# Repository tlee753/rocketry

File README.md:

# rocketry
Rocket Launch Code for Raspberry Pi Zero W

### Setup
1) install pip3
- `sudo apt install python3-pip`

2) install radio libraries
```bash
pip3 install board
pip3 install RPI.GPIO
pip3 install adafruit-blinka
pip3 install adafruit-circuitpython-rfm9x
```

3) enable SPI/I2C
- `sudo raspi-config`
  - `interface options`
- test with `python3 interfaceTest.py`

4) Connect Hardware
- `python3 pingTest.py`

5) Run python files at launch

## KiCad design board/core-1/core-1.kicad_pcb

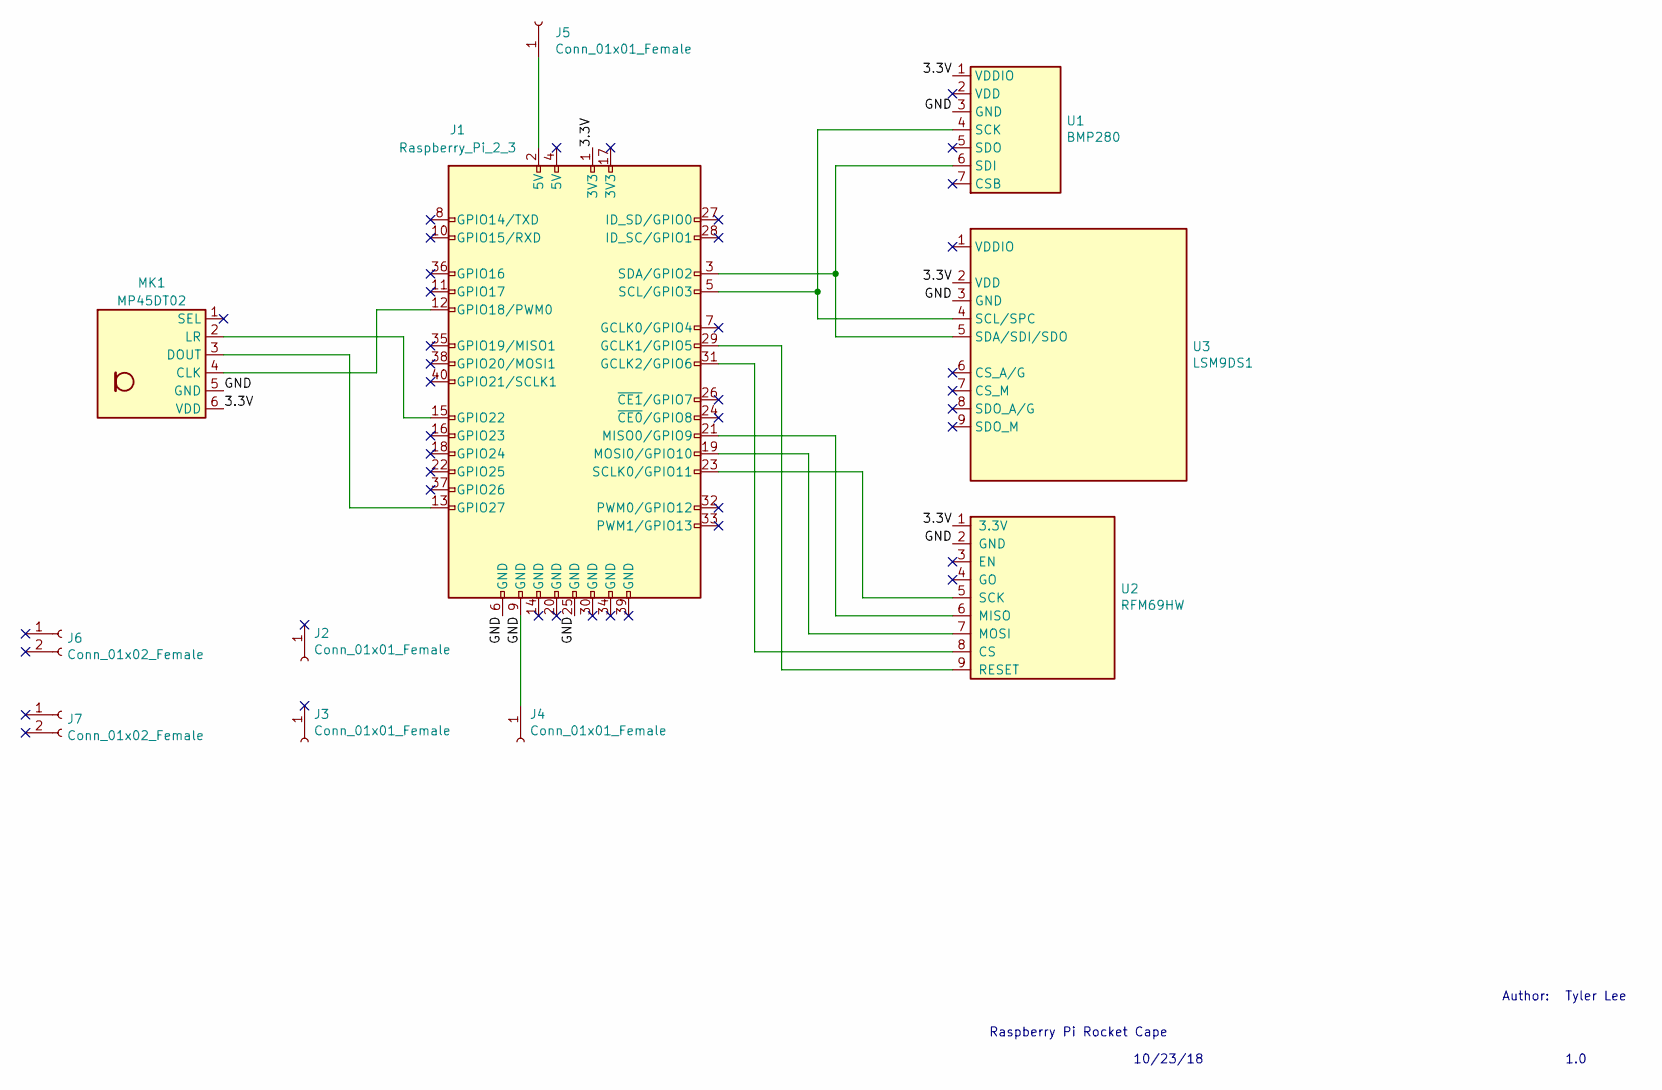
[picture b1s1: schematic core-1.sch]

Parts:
J1: Raspberry_Pi_2_3; IDC-Header_2x20_P2.54mm_Vertical
J2, J3, J4, J5: Conn_01x01_Female; PinHeader_1x01_P2.54mm_Horizontal
J6, J7: Conn_01x02_Female; PinHeader_1x02_P2.54mm_Horizontal
MK1: MP45DT02; PinHeader_1x06_P2.54mm_Vertical
U1: BMP280; PinHeader_1x07_P2.54mm_Vertical
U2: RFM69HW; PinSocket_1x09_P2.54mm_Vertical
U3: LSM9DS1; PinHeader_1x09_P2.54mm_Vertical

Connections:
/3.3V: J1.1 (3V3), MK1.6 (VDD), U1.1 (VDDIO), U2.1 (3.3V), U3.2 (VDD)
/GND: J1.6 (GND), J1.9 (GND), J1.25 (GND), J4.1, MK1.5 (GND), U1.3 (GND), U2.2 (GND), U3.3 (GND)
unnamed: J1.2 (5V), J5.1
unnamed: J1.3 (SDA/GPIO2), U1.6 (SDI), U3.5 (SDA/SDI/SDO)
unnamed: J1.5 (SCL/GPIO3), U1.4 (SCK), U3.4 (SCL/SPC)
unnamed: J1.12 (GPIO18/PWM0), MK1.4 (CLK)
unnamed: J1.13 (GPIO27), MK1.3 (DOUT)
unnamed: J1.15 (GPIO22), MK1.2 (LR)
unnamed: J1.19 (MOSI0/GPIO10), U2.7 (MOSI)
unnamed: J1.21 (MISO0/GPIO9), U2.6 (MISO)
unnamed: J1.23 (SCLK0/GPIO11), U2.5 (SCK)
unnamed: J1.29 (GCLK1/GPIO5), U2.9 (RESET)
unnamed: J1.31 (GCLK2/GPIO6), U2.8 (CS)

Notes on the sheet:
Raspberry Pi Rocket Cape
10/23/18
1.0
Tyler Lee
Author:

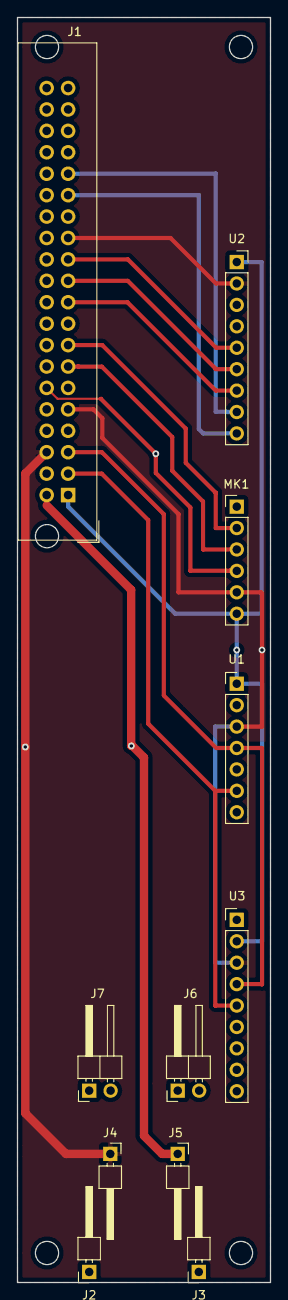
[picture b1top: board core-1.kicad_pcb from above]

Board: 2 copper layers, 30.0 x 150.0 mm, 11 parts (0 on the bottom side), 13 nets.

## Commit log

2018-04-29 init code
2018-04-29 getting closer
2018-04-29 documentation
2018-12-16 “updates”
